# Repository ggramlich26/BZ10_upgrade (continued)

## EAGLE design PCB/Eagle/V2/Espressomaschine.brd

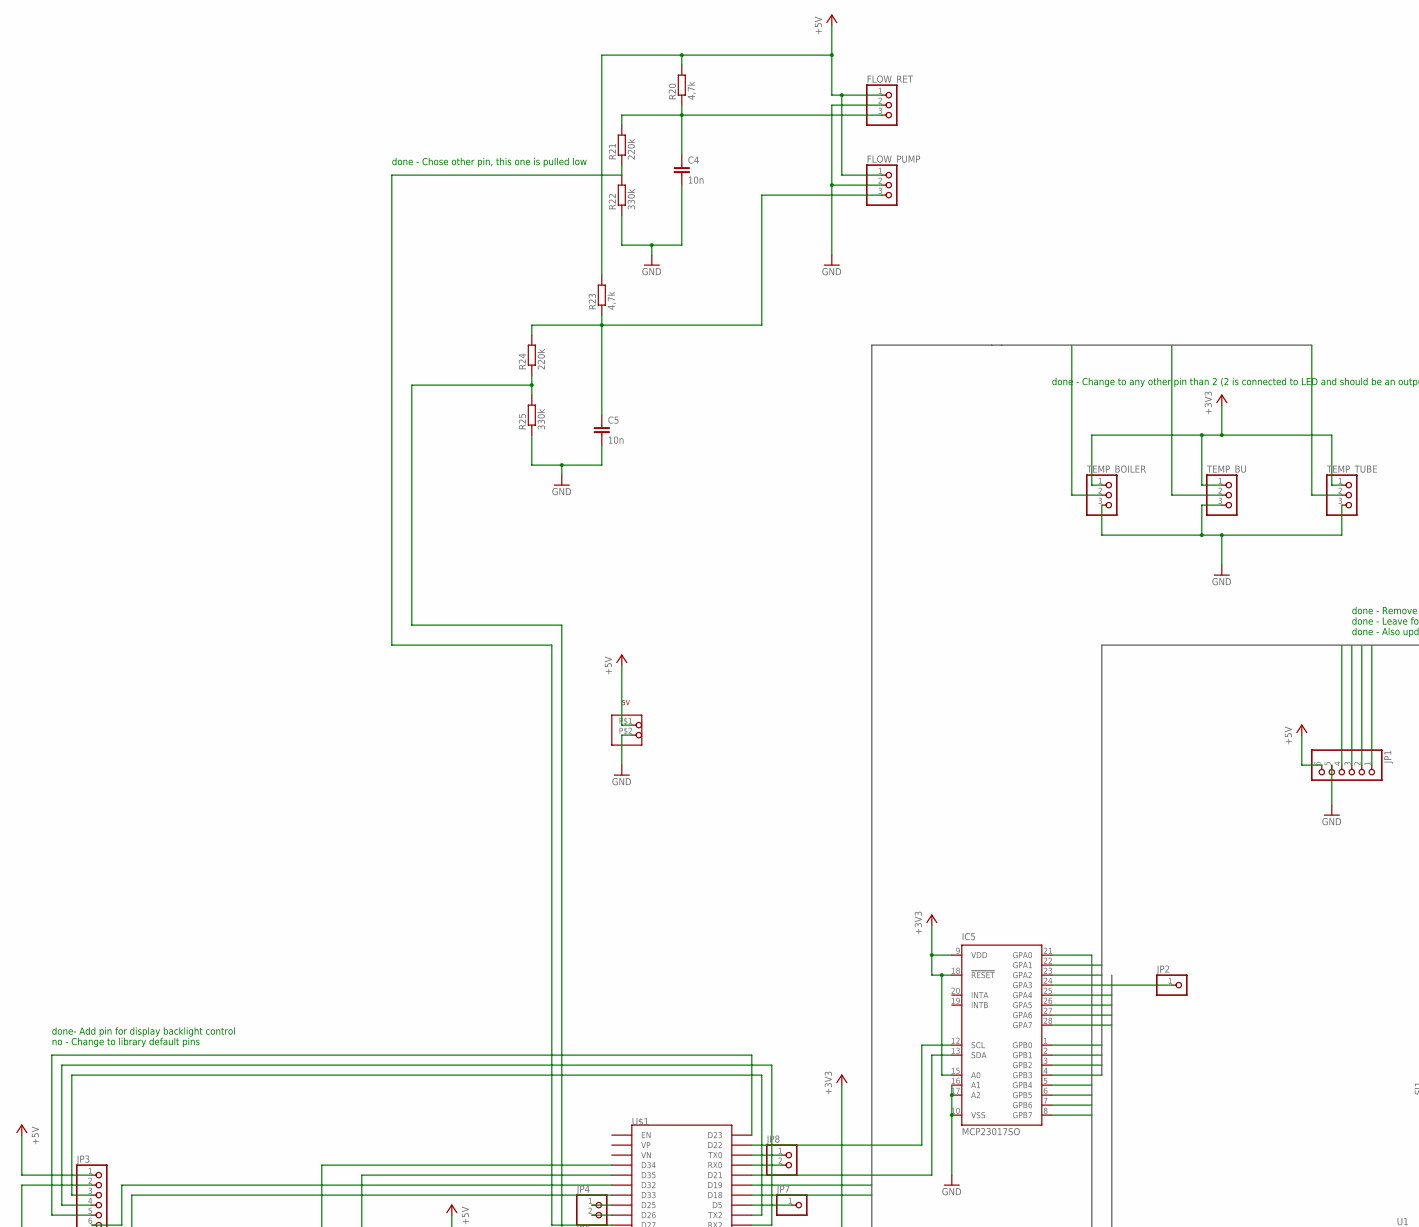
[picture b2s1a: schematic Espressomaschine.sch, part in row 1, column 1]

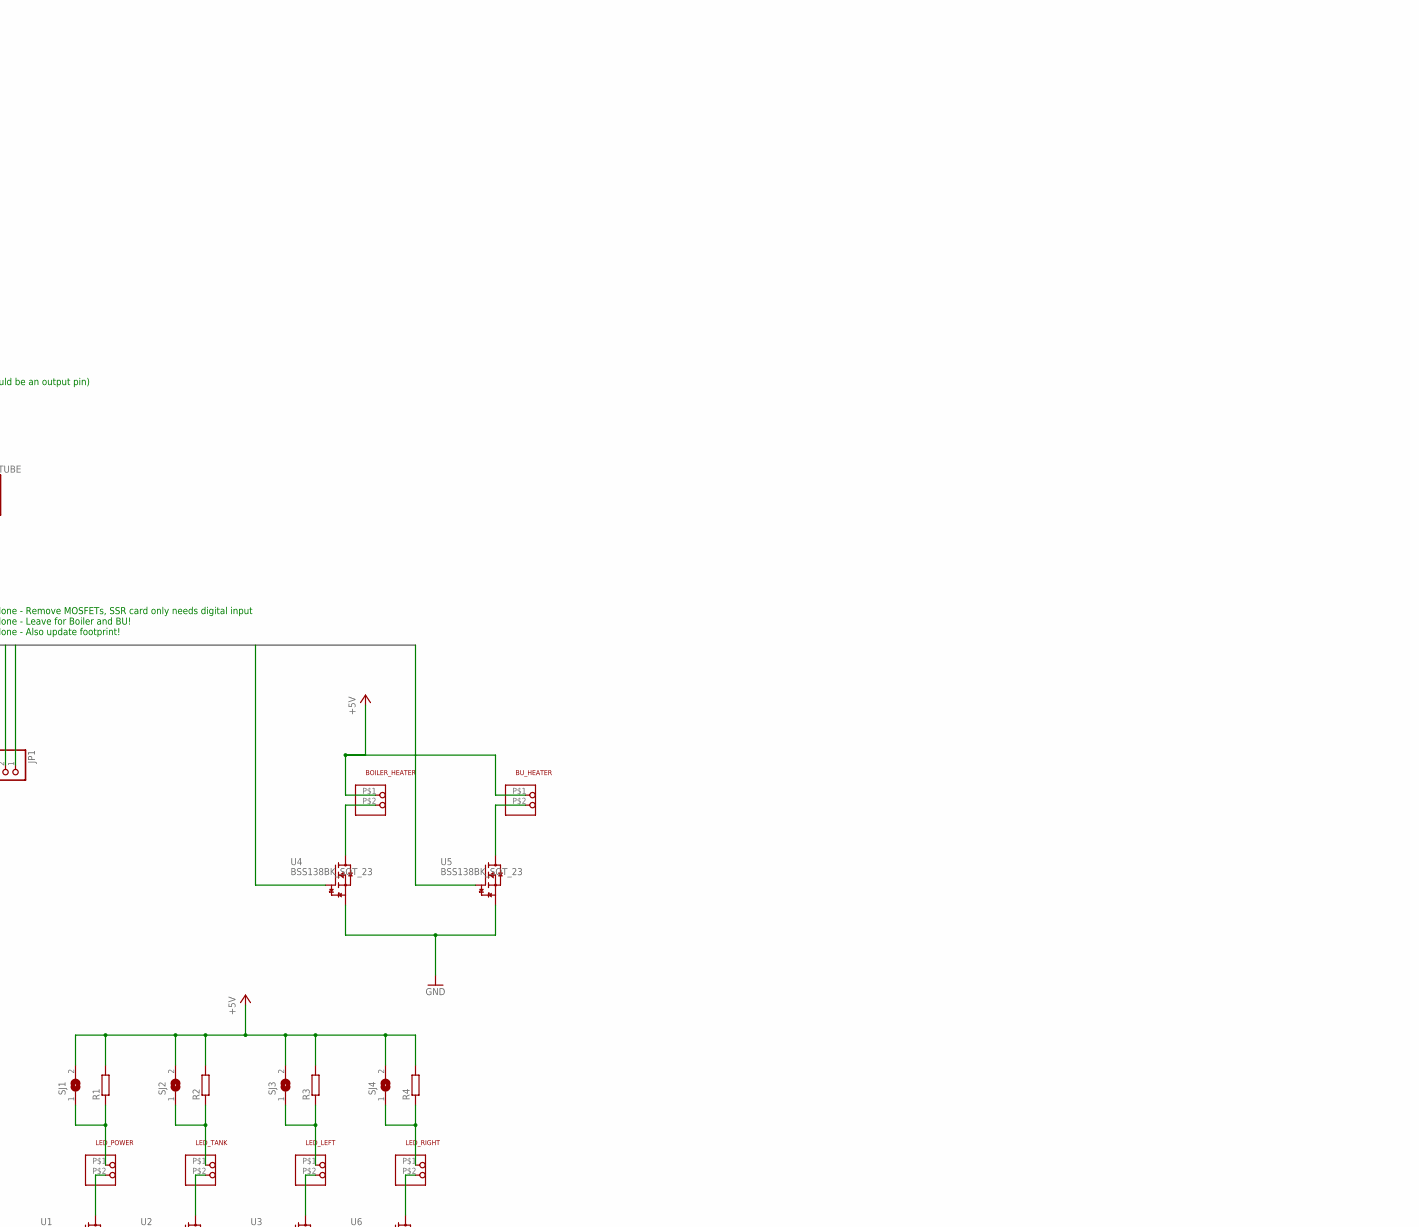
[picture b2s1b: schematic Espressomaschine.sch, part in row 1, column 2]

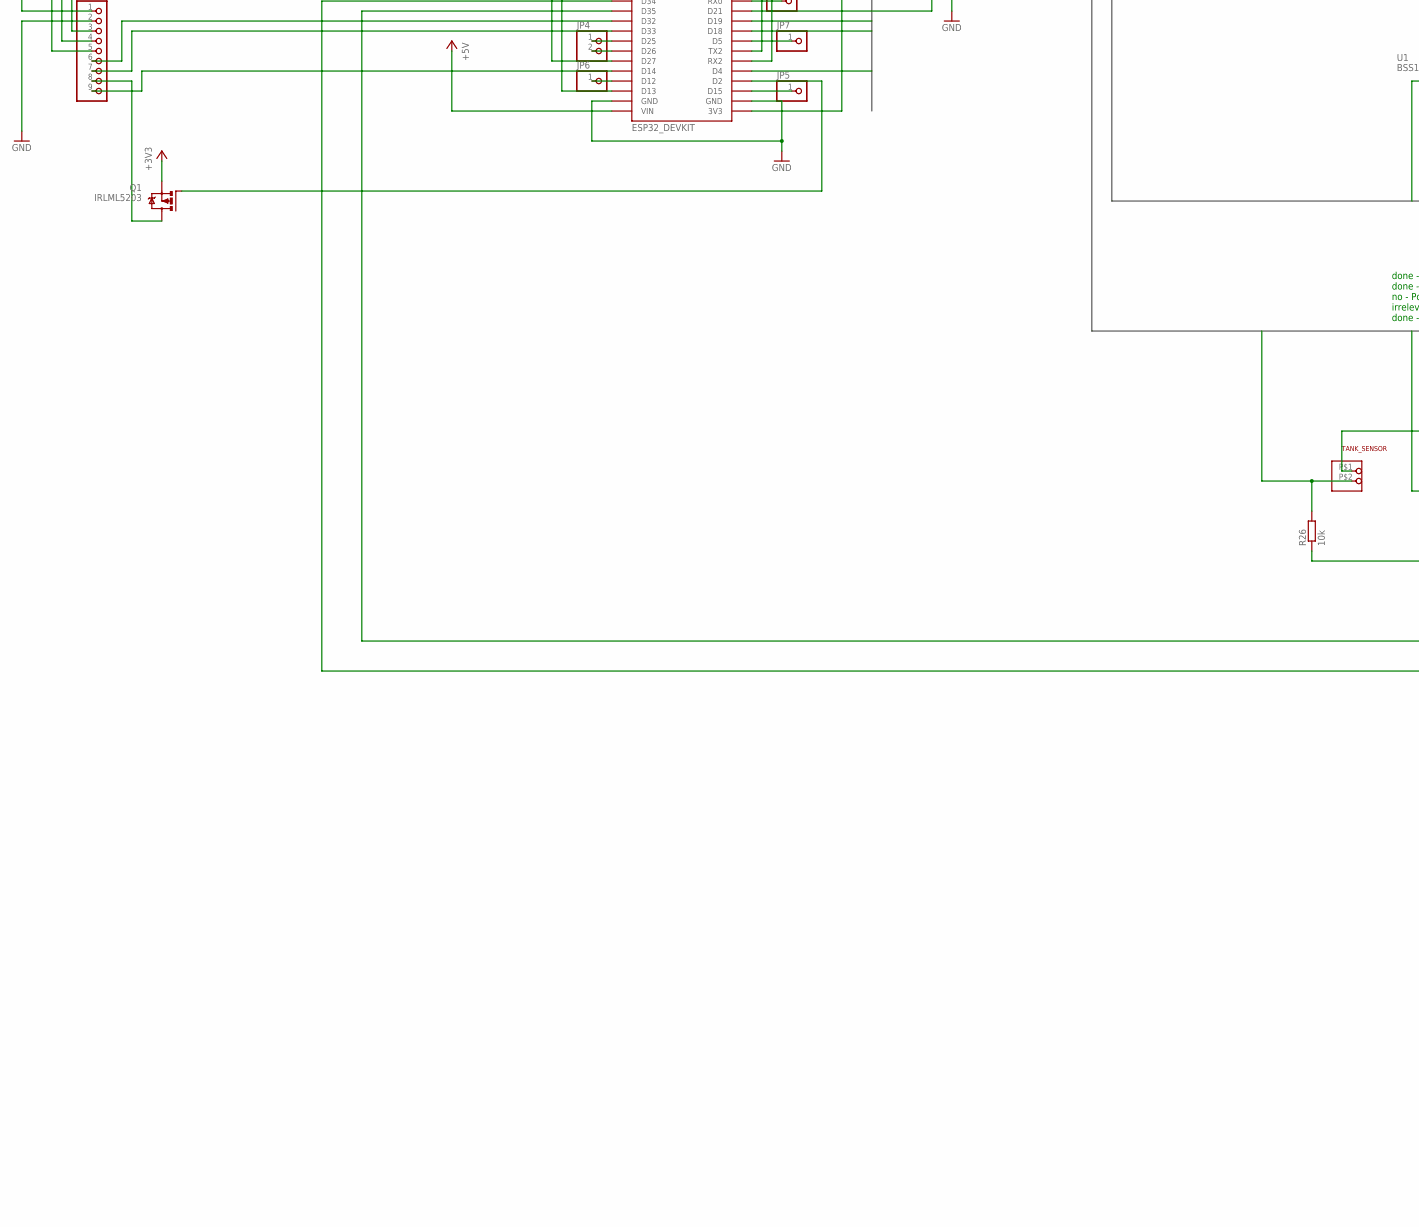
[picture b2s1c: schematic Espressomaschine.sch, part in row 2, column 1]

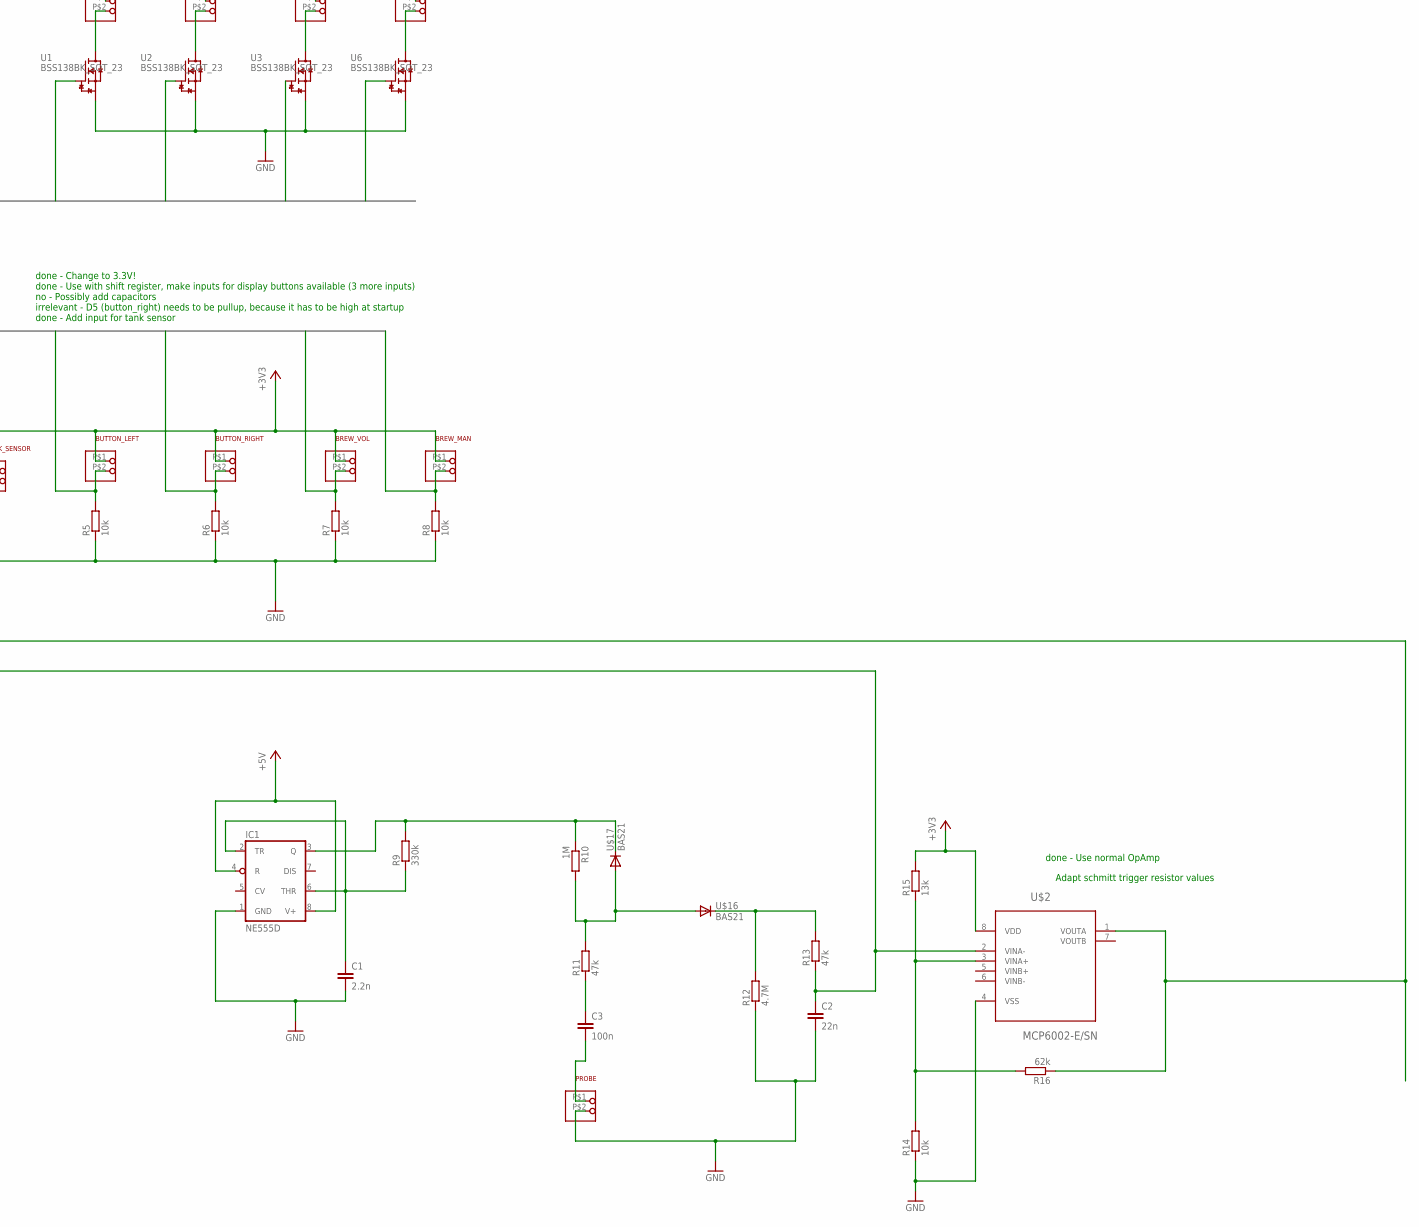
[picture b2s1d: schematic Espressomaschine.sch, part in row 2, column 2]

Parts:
5V: 1X2RM5; 1X02_RM5
BOILER_HEATER: 1X2RM5; 1X02_RM5
BREW_MAN: 1X2RM5; 1X02_RM5
BREW_VOL: 1X2RM5; 1X02_RM5
BUTTON_LEFT: 1X2RM5; 1X02_RM5
BUTTON_RIGHT: 1X2RM5; 1X02_RM5
BU_HEATER: 1X2RM5; 1X02_RM5
C1: 2.2n; C0603
C2: 22n; C0603
C3: 100n; C0603
C4, C5: 10n; C0603
FLOW_PUMP: PINHD-1X3; 1X03
FLOW_RET: PINHD-1X3; 1X03
IC1: NE555D; SO08
IC5: MCP23017SO; SO28W
JP1: PINHD-1X6; 1X06
JP2, JP5, JP6, JP7: PINHD-1X1; 1X01
JP3: PINHD-1X9; 1X09
JP4, JP8: PINHD-1X2; 1X02
LED_LEFT: 1X2RM5; 1X02_RM5
LED_POWER: 1X2RM5; 1X02_RM5
LED_RIGHT: 1X2RM5; 1X02_RM5
LED_TANK: 1X2RM5; 1X02_RM5
PROBE: 1X2RM5; 1X02_RM5
Q1: IRLML5203; MICRO3
R1, R2, R3, R4: R-EU_R0603; R0603
R5, R6, R7, R8, R14, R26: 10k; R0603
R9, R22, R25: 330k; R0603
R10: 1M; R0603
R11, R13: 47k; R0603
R12: 4.7M; R0603
R15: 13k; R0603
R16: 62k; R0603
R20, R23: 4,7k; R0603
R21, R24: 220k; R0603
SJ1, SJ2, SJ3, SJ4: SJ
TANK_SENSOR: 1X2RM5; 1X02_RM5
TEMP_BOILER: PINHD-1X3; 1X03
TEMP_BU: PINHD-1X3; 1X03
TEMP_TUBE: PINHD-1X3; 1X03
U1, U2, U3, U4, U5, U6: BSS138BK_SOT_23; SOT23
U$1: ESP32_DEVKIT
U$2: MCP6002-E/SN; SOIC127P600X175-8N
U$16, U$17: BAS21; SOT23

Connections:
+3V3: BREW_MAN.P$1 (1), BREW_VOL.P$1 (1), BUTTON_LEFT.P$1 (1), BUTTON_RIGHT.P$1 (1), IC5.9 (VDD), IC5.15 (A0), IC5.18 (!RESET), Q1.2 (S), R15.2, TANK_SENSOR.P$1 (1), TEMP_BOILER.1, TEMP_BU.1, TEMP_TUBE.1, U$1.3V3, U$2.8 (VDD)
+5V: 5V.P$1 (1), BOILER_HEATER.P$1 (1), BU_HEATER.P$1 (1), FLOW_PUMP.1, FLOW_RET.1, IC1.4 (R), IC1.8 (V+), JP1.6, JP3.1, R1.2, R2.2, R3.2, R4.2, R20.2, R23.2, SJ1.2, SJ2.2, SJ3.2, SJ4.2, U$1.VIN
BOILER_HEATER: IC5.23 (GPA2), U4.1 (G)
BOILER_VALVE: IC5.1 (GPB0), JP1.4
BREW_MAN: BREW_MAN.P$2 (2), IC5.8 (GPB7), R8.2
BREW_VOL: BREW_VOL.P$2 (2), IC5.7 (GPB6), R7.2
BUTTON_LEFT: BUTTON_LEFT.P$2 (2), IC5.6 (GPB5), R5.2
BUTTON_RIGHT: BUTTON_RIGHT.P$2 (2), IC5.5 (GPB4), R6.2
BU_HEATER: IC5.22 (GPA1), U5.1 (G)
BU_VALVE: IC5.2 (GPB1), JP1.3
EXP_VALVE: IC5.4 (GPB3), JP1.1
GND: 5V.P$2 (2), C1.2, C2.2, C4.2, C5.2, FLOW_PUMP.2, FLOW_RET.2, IC1.1 (GND), IC5.10 (VSS), IC5.16 (A1), IC5.17 (A2), JP1.5, JP3.2, PROBE.P$2 (2), R5.1, R6.1, R7.1, R8.1, R12.1, R14.1, R22.1, R25.1, R26.1, TEMP_BOILER.3, TEMP_BU.3, TEMP_TUBE.3, U1.2 (S), U2.2 (S), U3.2 (S), U4.2 (S), U5.2 (S), U6.2 (S), U$1.GND@1 (GND), U$1.GND@2 (GND), U$2.4 (VSS)
LED_LEFT: IC5.25 (GPA4), U3.1 (G)
LED_POWER: IC5.26 (GPA5), U1.1 (G)
LED_RIGHT: IC5.28 (GPA7), U6.1 (G)
LED_TANK: IC5.27 (GPA6), U2.1 (G)
unnamed: LED_POWER.P$1 (1), R1.1, SJ1.1
unnamed: LED_TANK.P$1 (1), R2.1, SJ2.1
unnamed: LED_LEFT.P$1 (1), R3.1, SJ3.1
unnamed: Q1.1 (G), U$1.D2
unnamed: LED_RIGHT.P$2 (2), U6.3 (D)
unnamed: LED_LEFT.P$2 (2), U3.3 (D)
unnamed: BOILER_HEATER.P$2 (2), U4.3 (D)
unnamed: BU_HEATER.P$2 (2), U5.3 (D)
unnamed: LED_RIGHT.P$1 (1), R4.1, SJ4.1
unnamed: C1.1, IC1.2 (TR), IC1.6 (THR), R9.1
unnamed: R10.2, R11.2, U$16.1 (A), U$17.1 (A)
unnamed: C3.1, R11.1
unnamed: IC1.3 (Q), R9.2, R10.1, U$17.3 (C)
unnamed: R12.2, R13.2, U$16.3 (C)
unnamed: C2.1, R13.1, U$1.D34, U$2.2 (VINA-)
unnamed: R14.2, R15.1, R16.2, U$2.3 (VINA+)
unnamed: C3.2, PROBE.P$1 (1)
unnamed: R16.1, U$1.D35, U$2.1 (VOUTA)
unnamed: IC5.24 (GPA3), JP2.1
unnamed: JP7.1, U$1.D5
unnamed: LED_TANK.P$2 (2), U2.3 (D)
unnamed: IC5.12 (SCL), U$1.D22
unnamed: LED_POWER.P$2 (2), U1.3 (D)
unnamed: JP3.8, Q1.3 (D)
unnamed: JP4.1, U$1.D25
unnamed: JP3.3, U$1.TX2
unnamed: JP3.4, U$1.RX2
unnamed: JP3.5, U$1.D23
unnamed: JP3.6, U$1.D32
unnamed: JP3.7, U$1.D33
unnamed: JP3.9, U$1.D14
unnamed: C4.1, FLOW_RET.3, R20.1, R21.2
unnamed: C5.1, FLOW_PUMP.3, R23.1, R24.2
unnamed: IC5.13 (SDA), U$1.D21
unnamed: R21.1, R22.2, U$1.D27
unnamed: JP4.2, U$1.D26
unnamed: JP5.1, U$1.D15
unnamed: R24.1, R25.2, U$1.D13
unnamed: JP6.1, U$1.D12
unnamed: JP8.1, U$1.TX0
unnamed: JP8.2, U$1.RX0
PUMP: IC5.3 (GPB2), JP1.2
TANK_SENSOR: IC5.21 (GPA0), R26.2, TANK_SENSOR.P$2 (2)
TEMP_BOILER: TEMP_BOILER.2, U$1.D19
TEMP_BU: TEMP_BU.2, U$1.D4
TEMP_TUBE: TEMP_TUBE.2, U$1.D18

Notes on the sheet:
done - Change to 3.3V! done - Use with shift register, make inputs for display buttons available (3 more inputs) no - Possibly add capacitors irrelevant - D5 (button_right) needs to be pullup, because it has to be high at startup done - Add input for tank sensor
done - Change to any other pin than 2 (2 is connected to LED and should be an output pin)
done - Remove MOSFETs, SSR card only needs digital input done - Leave for Boiler and BU! done - Also update footprint!
done - Chose other pin, this one is pulled low
done- Add pin for display backlight control no - Change to library default pins
done - Use normal OpAmp
Adapt schmitt trigger resistor values

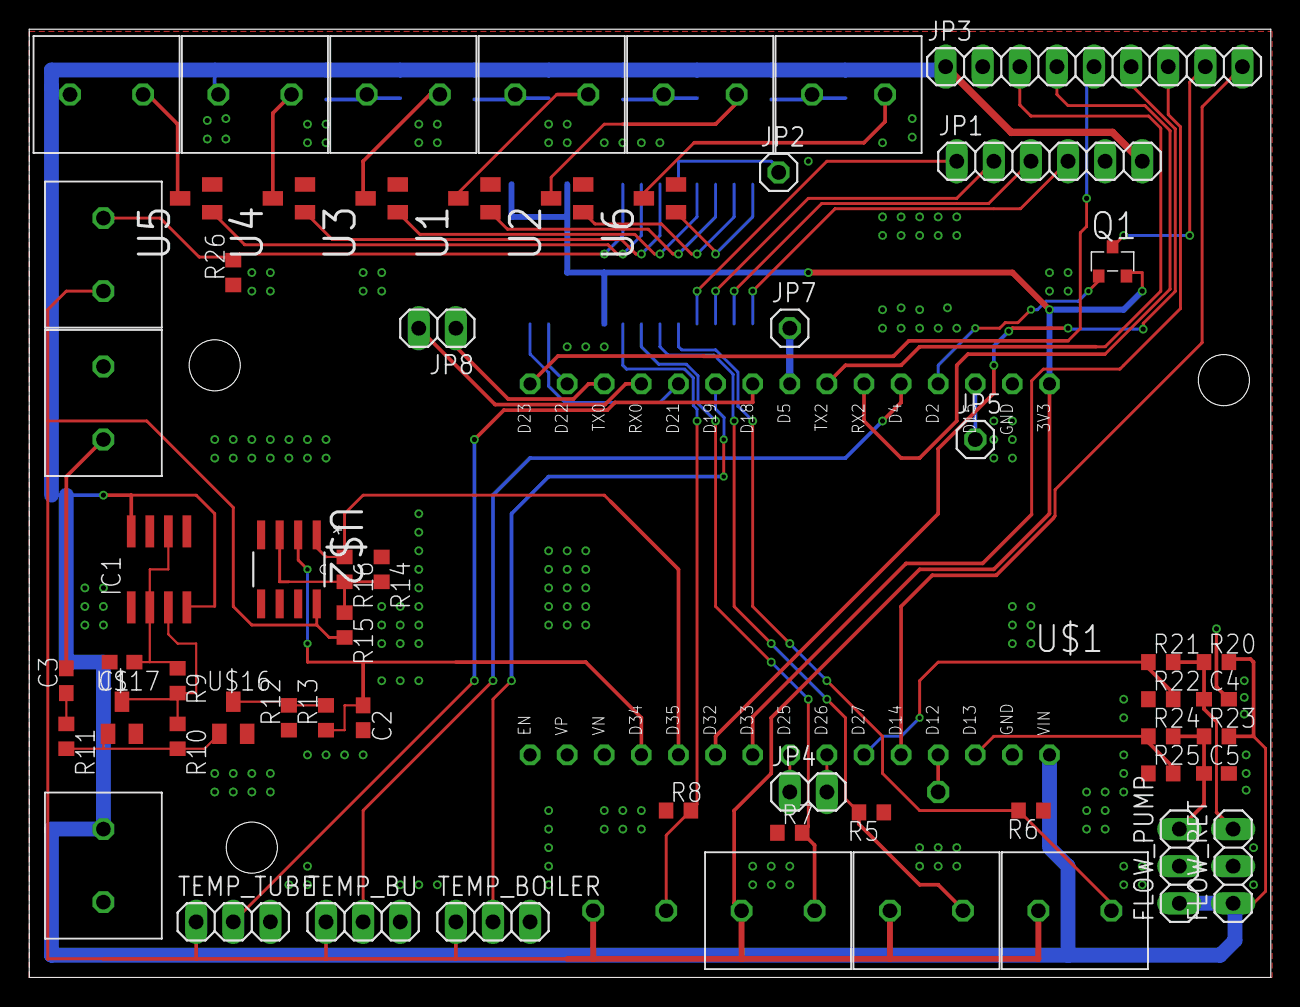
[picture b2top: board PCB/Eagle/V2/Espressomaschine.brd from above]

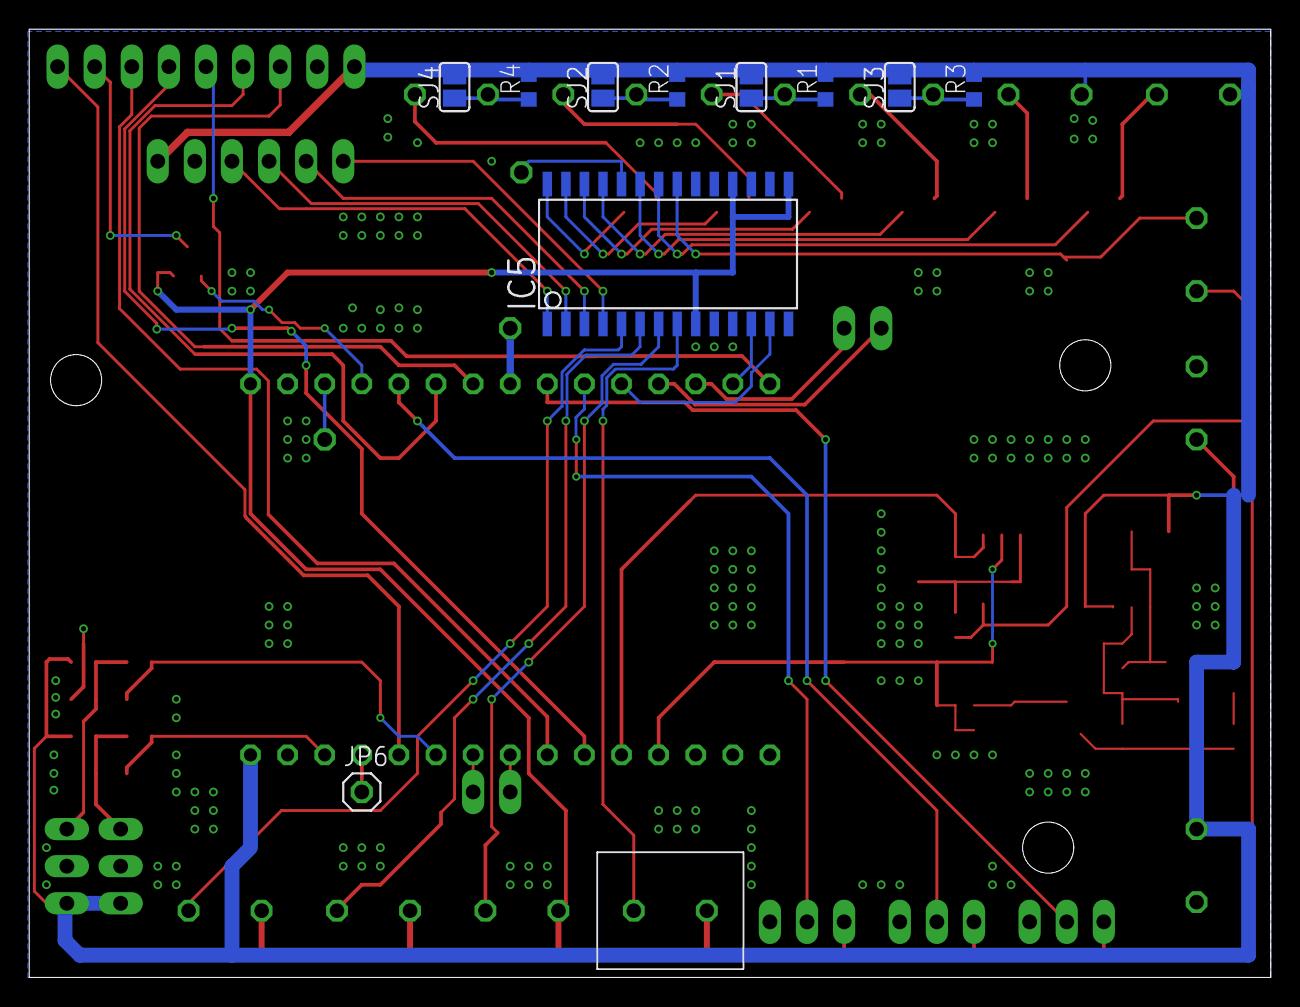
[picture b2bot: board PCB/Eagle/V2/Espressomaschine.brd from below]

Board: 2 copper layers, 85.0 x 64.9 mm, 71 parts (11 on the bottom side), 62 nets.

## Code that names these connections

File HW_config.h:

/*
 * device_config.h
 *
 *  Created on: May 30, 2020
 *      Author: tsugua
 */

#ifndef HW_CONFIG_H_
#define HW_CONFIG_H_

#include "ADS1115_WE.h"

#define SR_SER				22
#define	SR_SCK				19
#define	SR_RCK				21

#define MCP_SCL				22
#define MCP_SDA				21
#define MCP_ADDR			0x21
#define ADS_ADDR			0x48
#define ADS_RDY				12
#define ADS_SAMPLE_INTERVAL	100		//sample interval in ms

#define	BU_VALVE			9
#define BU_VALVE_LOW_LEVEL_TRIGGER
#define	BOILER_VALVE		8
#define BOILER_VALVE_LOW_LEVEL_TRIGGER
#define	PUMP				10
#define PUMP_LOW_LEVEL_TRIGGER
#define	BOILER_HEATER		2
//#define BOILER_HEATER_LOW_LEVEL_TRIGGER
#define	BU_HEATER			11
#define BU_HEATER_LOW_LEVEL_TRIGGER
#define	EXP_VALVE			1
#define EXP_VALVE_LOW_LEVEL_TRIGGER

#define	LED_LEFT			4
#define	LED_POWER			5
#define	LED_TANK			6
#define	LED_RIGHT			7

#define BOILER_TEMP_ON_ADS	//comment to use TSIC for boiler temperature
#define ADS_BOILER_INPUT	ADS1115_COMP_0_GND
#define ADS_BOILER_MAX_VOLT	ADS1115_RANGE_4096
#define ADS_VCC_INPUT		ADS1115_COMP_1_GND
#define ADS_VCC_MAX_VOLT	ADS1115_RANGE_2048
#define ADS_VCC_CONV_FACTOR	2	//(R27+R28)/R28
#define ADS_BOILER_REF_R	22e3	//R29
//calculate NTC temperature:	(see Wikipedia)
// 1/T = 1/TN + 1/B*ln(RT/RN) with
// T:	temperature
// TN:	reference temperature
// B:	conversion factor
// RT:	NTC resistance at T
// RN:	NTC resistance at TN
#define ADS_BOILER_B		4458	//factor for calculation of NTC temperature
#define ADS_BOILER_TN		373.15	//reference temperature: 100 degree celsius
#define ADS_BOILER_RN		1.12e3	//resistance at TN
#define ADS_T0				273.15	//0 degree celsius in Kelvin for convenience
//TSIC pins:
#define	TEMP_BOILER_PIN		19
#define	TEMP_BU_PIN			4
#define	TEMP_TUBE_PIN		18

#define	BUTTON_LEFT_PIN		13
#define	BUTTON_RIGHT_PIN	12
#define	BREW_VOL_PIN		14
#define	BREW_MAN_PIN		15
#define TANK_PIN			0

#define	FLOW_PUMP_PIN		13
#define	FLOW_RET_PIN		27

#define	PROBE_ANALOG_PIN	34
#define	PROBE_DIGITAL_PIN	35

#define TFT_DC 		23
#define TFT_CS 		17
#define	TFT_MOSI	32
#define	TFT_CLK		33
#define	TFT_MISO	14
#define TFT_RST		16
#define TFT_LED		2

#endif /* HW_CONFIG_H_ */

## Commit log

2020-08-25 Got a lot of stuff working (forgot I had this on git before)
2020-08-25 fixed displayed temperatures
2020-08-30 Added P controller behavior for both heaters
2020-08-30 Added comments and tidied up
2020-09-19 Added flowmeter support
2020-09-25 Added state machine visual documentation
2020-09-26 Adding standbye functionality part 1
2020-10-02 Added temperature error state
2020-10-02 Added error message on display for temperature sensor error
2020-10-02 disabling heaters in standbye and on errors
2020-10-12 Added preinfusion and automated cleaning capability
2020-10-13 Disabling and enabling Blynk is now possible
2020-10-13 Workaround for right button only working as pullup
2020-10-17 Made preinfusion and standby variables available through Blynk
2020-10-25 minor improvements
2020-11-15 README.md updated from https://stackedit.io/
2020-11-22 running on Hardware V2 now
2020-11-22 No preinfusion in manual distribution mode
2020-11-22 Added wifi credentials setup mode
2020-11-23 wake up from standby time now stored in presistent memory
2020-12-10 Minor fixes
2020-12-16 added build variable or boiler heater quick start. Disabled quick start
2020-12-16 Made flow sensor tick to volume conversion rates adjustable through Blynk
2020-12-16 Updated default values for boiler heater and flow sensors
2020-12-17 Added time counting after preinfusion capability
2020-12-19 Fixed volumetric distribution with preinfusion
2020-12-23 first try for debouncing buttons
2020-12-23 Better button debouncing
2021-02-10 Change: PID instead of P controller
2021-02-15 added photos of mod
2021-02-18 Added PCB files
2021-02-23 Added LTSpice simulation for boiler probe
2021-03-03 PCB for for external antenna and with NTC connectors
2021-03-04 Finalized PCB V3
2021-03-29 improved default values
2021-03-29 ADD: ADS1115 for boiler temperature measurement
2021-03-29 ADD: lcd-image-converter and custom profile
2021-05-10 minor improvements for NTC
2022-04-30 CHANGE: made time variables of type unsigned long
2022-04-30 CHANGE: Fixed getting stuck in Blynk loop when internet down
    Replaced the blocking Blynk.connect() with a non-blocking version, that
    also is non-blocking, if wifi is available but the internet is down.
2023-03-18 adapted to new blynk version
2023-03-18 switched from Blynk to webserver
2023-03-19 new icons for wifi connected and hotspot. Disabling wifi working now. wakeup time working now.
2023-03-19 Webserver instead of Blynk
